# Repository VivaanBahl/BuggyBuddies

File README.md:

# BuggyBuddies
buggy buddies!

LPC Projects: Contains all of the projects that can be opened in LPCXpresso. Each project corresponds to a software component of the buggy.

PWM_Sample: code for the steering controller

Collision_Avoidance: code for the ultrasonic

pwmdemodulator: code for the radio receiver

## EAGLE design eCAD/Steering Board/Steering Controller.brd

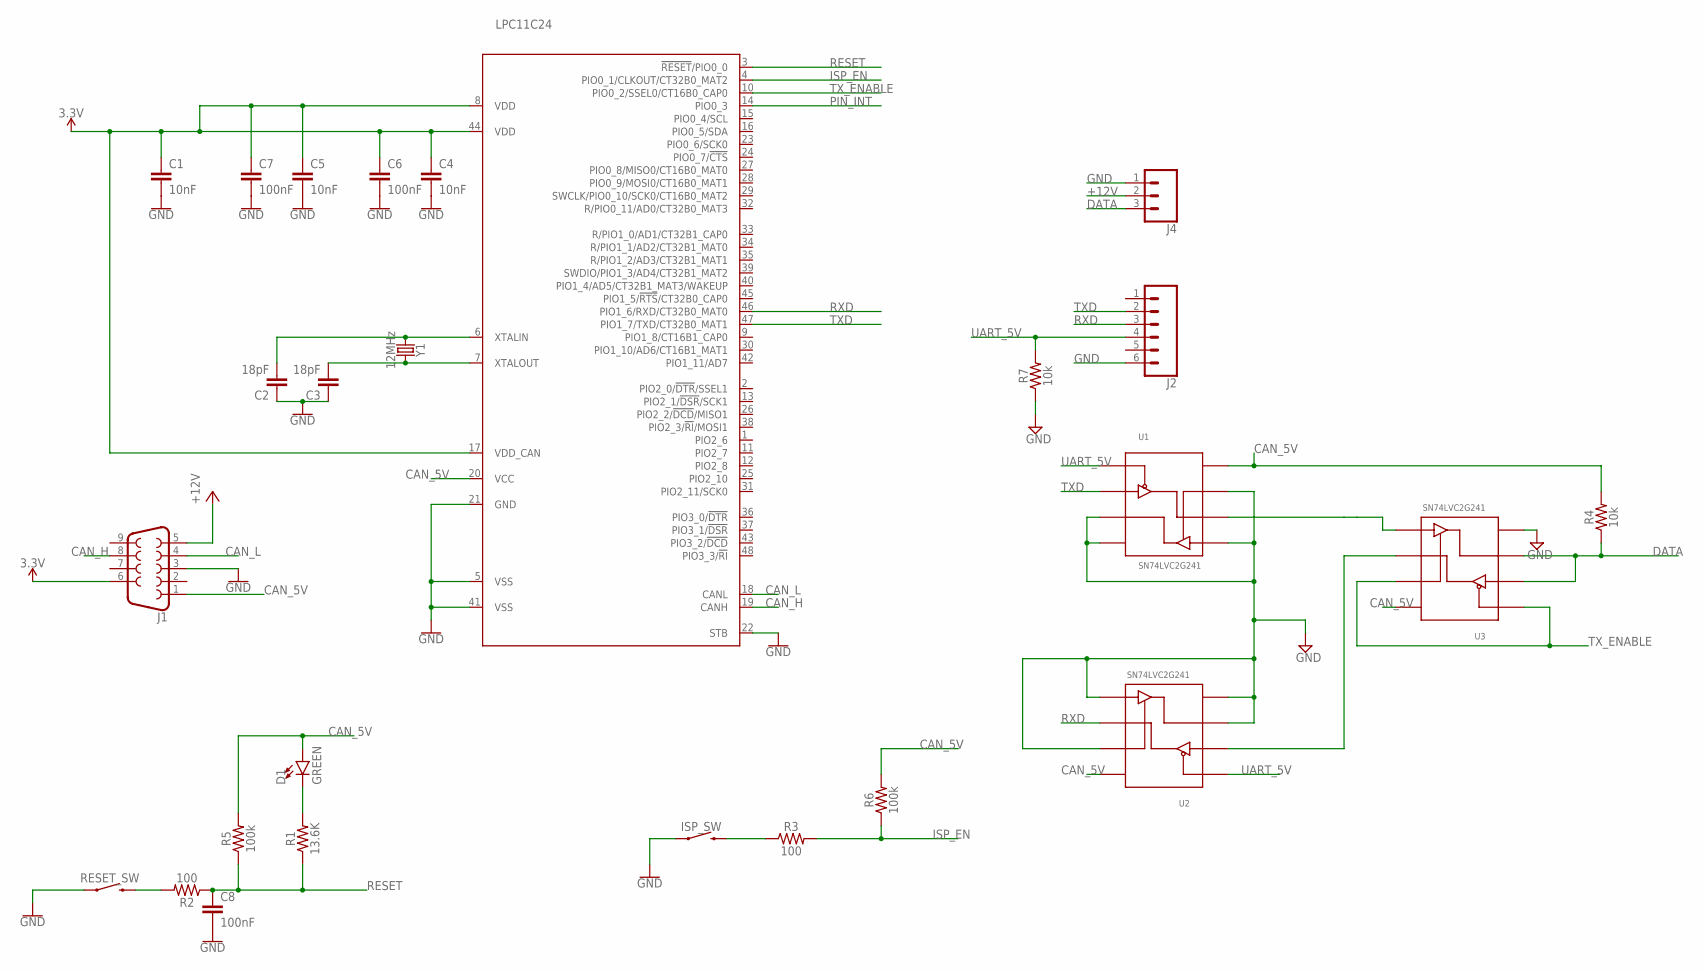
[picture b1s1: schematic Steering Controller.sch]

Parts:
C1, C4, C5: 10nF; CAP-PTH-2.54
C2, C3: 18pF; CAP-PTH-2.54
C6, C7, C8: 100nF; CAP-PTH-2.54
D1: GREEN; LED-1206
ISP_SW: MOMENTARY-SWITCH-SPST-PTH-6.0MM; TACTILE_SWITCH_PTH_6.0MM
J1: DB9FEMALE; DB9
J2: CONN_06SILK_FEMALE_PTH; 1X06
J4: CONN_03; 1X03
LPC11C24: LPC11C22/24-LQFP48; LQFP48
R1: 13.6K; AXIAL-0.3
R2, R3: 100; AXIAL-0.3
R4, R7: 10k; AXIAL-0.3
R5, R6: 100k; AXIAL-0.3
RESET_SW: MOMENTARY-SWITCH-SPST-PTH-6.0MM; TACTILE_SWITCH_PTH_6.0MM
U1, U2, U3: SN74LVC2G241; TI_S8
Y1: 12MHz; HC49US

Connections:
3.3V: C1.1, C4.1, C5.1, C6.1, C7.1, J1.6, LPC11C24.8 (VDD), LPC11C24.17 (VDD_CAN), LPC11C24.44 (VDD)
+12V: J1.5, J4.2
CAN_5V: D1.A, J1.1, LPC11C24.20 (VCC), R4.P$2 (2), R5.P$2 (2), R6.P$2 (2), U1.8 (VCC), U2.8 (VCC), U3.8 (VCC)
CAN_H: J1.8, LPC11C24.19 (CANH)
CAN_L: J1.4, LPC11C24.18 (CANL)
DATA: J4.3, R4.P$1 (1), U3.2 (1IN), U3.3 (2OUT)
GND: C1.2, C2.1, C3.1, C4.2, C5.2, C6.2, C7.2, C8.2, ISP_SW.1, J1.3, J2.6, J4.1, LPC11C24.5 (VSS), LPC11C24.21 (GND), LPC11C24.22 (STB), LPC11C24.41 (VSS), R7.P$1 (1), RESET_SW.1, U1.3 (2OUT), U1.4 (GND), U1.5 (2IN), U1.7 (2OE), U2.3 (2OUT), U2.4 (GND), U2.5 (2IN), U2.7 (2OE), U3.4 (GND)
ISP_EN: LPC11C24.4 (PIO0_1/CLKOUT/CT32B0_MAT2), R3.P$2 (2), R6.P$1 (1)
unnamed: D1.C, R1.P$2 (2)
unnamed: R2.P$2 (2), RESET_SW.3 (2)
unnamed: U2.2 (1IN), U3.6 (1OUT)
unnamed: ISP_SW.3 (2), R3.P$1 (1)
unnamed: U1.6 (1OUT), U3.5 (2IN)
PIN_INT: LPC11C24.14 (PIO0_3)
RESET: C8.1, LPC11C24.3 (!RESET!/PIO0_0), R1.P$1 (1), R2.P$1 (1), R5.P$1 (1)
RXD: J2.3, LPC11C24.46 (PIO1_6/RXD/CT32B0_MAT0), U2.6 (1OUT)
TXD: J2.2, LPC11C24.47 (PIO1_7/TXD/CT32B0_MAT1), U1.2 (1IN)
TX_ENABLE: LPC11C24.10 (PIO0_2/SSEL0/CT16B0_CAP0), U3.1 (~1OE), U3.7 (2OE)
UART_5V: J2.4, R7.P$2 (2), U1.1 (~1OE), U2.1 (~1OE)
XTALIN: C2.2, LPC11C24.6 (XTALIN), Y1.1
XTALOUT: C3.2, LPC11C24.7 (XTALOUT), Y1.2

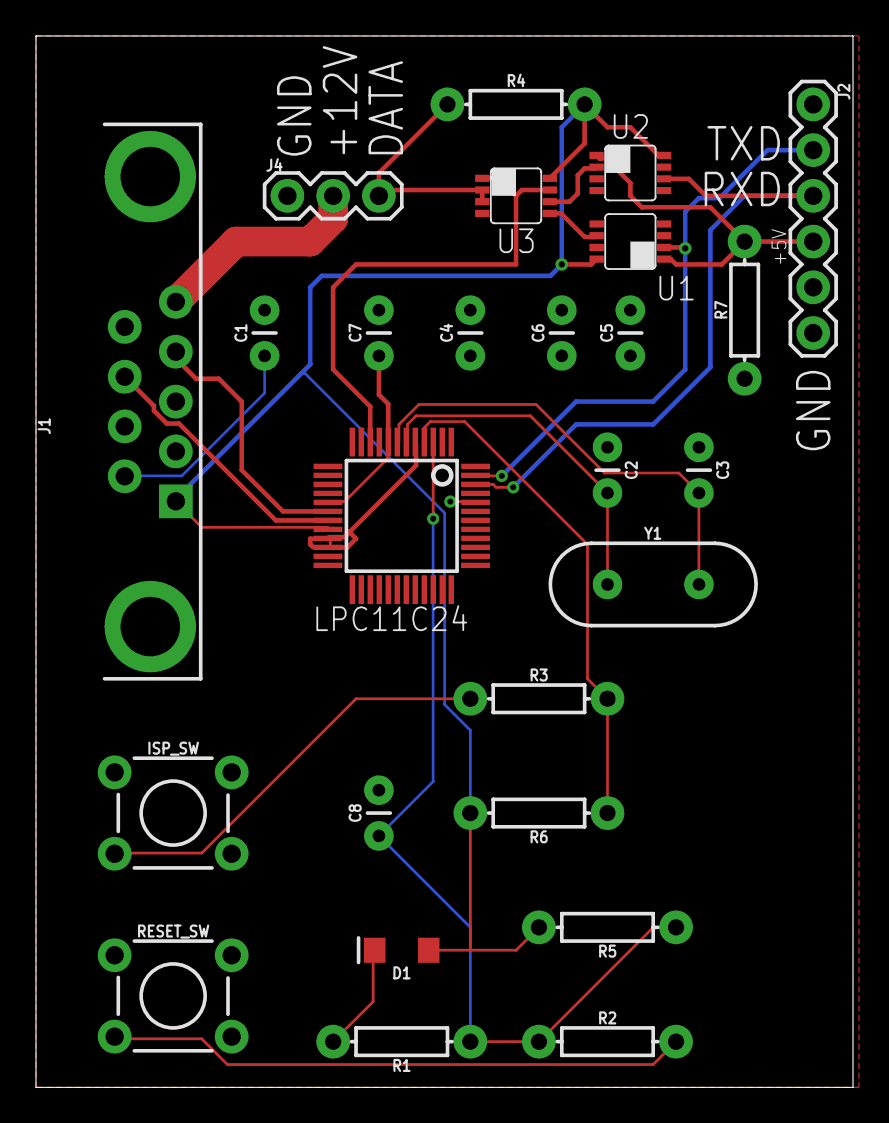
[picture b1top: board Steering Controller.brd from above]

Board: 2 copper layers, 45.4 x 58.4 mm, 26 parts (0 on the bottom side), 20 nets.

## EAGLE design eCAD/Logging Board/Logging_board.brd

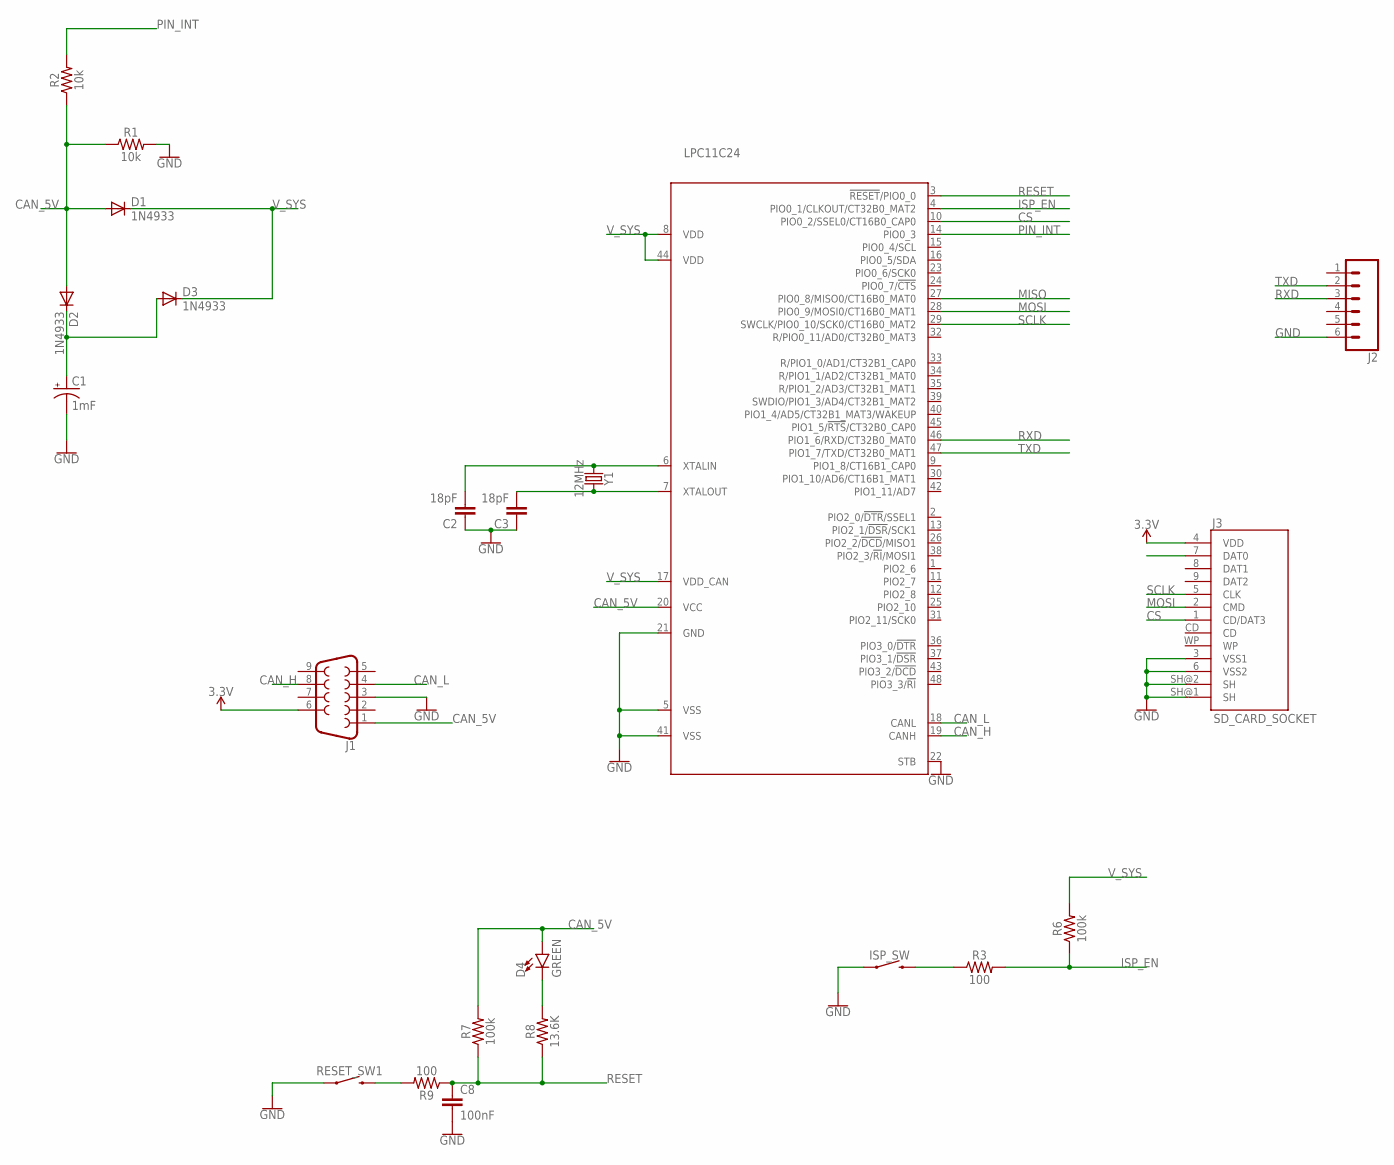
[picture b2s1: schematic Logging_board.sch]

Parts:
C1: 1mF; CPOL-RADIAL-5MM-10MM
C2, C3: 18pF; CAP-PTH-2.54
C8: 100nF; CAP-PTH-2.54
D1, D2, D3: 1N4933; DO41-10
D4: GREEN; LED-1206
ISP_SW: MOMENTARY-SWITCH-SPST-PTH-6.0MM; TACTILE_SWITCH_PTH_6.0MM
J1: DB9FEMALE; DB9
J2: CONN_06SILK_FEMALE_PTH; 1X06
J3: SD_CARD_SOCKET; SD
LPC11C24: LPC11C22/24-LQFP48; LQFP48
R1, R2: 10k; AXIAL-0.3
R3, R9: 100; AXIAL-0.3
R6, R7: 100k; AXIAL-0.3
R8: 13.6K; AXIAL-0.3
RESET_SW1: MOMENTARY-SWITCH-SPST-PTH-6.0MM; TACTILE_SWITCH_PTH_6.0MM
Y1: 12MHz; HC49US

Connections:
3.3V: J1.6, J3.4 (VDD)
CAN_5V: D1.A, D2.A, D4.A, J1.1, LPC11C24.20 (VCC), R1.P$1 (1), R2.P$1 (1), R7.P$2 (2)
CAN_H: J1.8, LPC11C24.19 (CANH)
CAN_L: J1.4, LPC11C24.18 (CANL)
CS: J3.1 (CD/DAT3), LPC11C24.10 (PIO0_2/SSEL0/CT16B0_CAP0)
GND: C1.-, C2.1, C3.1, C8.2, ISP_SW.1, J1.3, J2.6, J3.3 (VSS1), J3.6 (VSS2), J3.SH@1 (SH), J3.SH@2 (SH), LPC11C24.5 (VSS), LPC11C24.21 (GND), LPC11C24.22 (STB), LPC11C24.41 (VSS), R1.P$2 (2), RESET_SW1.1
ISP_EN: LPC11C24.4 (PIO0_1/CLKOUT/CT32B0_MAT2), R3.P$2 (2), R6.P$1 (1)
MISO: LPC11C24.27 (PIO0_8/MISO0/CT16B0_MAT0)
MOSI: J3.2 (CMD), LPC11C24.28 (PIO0_9/MOSI0/CT16B0_MAT1)
unnamed: C1.+, D2.C, D3.A
unnamed: ISP_SW.3 (2), R3.P$1 (1)
unnamed: D4.C, R8.P$2 (2)
unnamed: R9.P$2 (2), RESET_SW1.3 (2)
PIN_INT: LPC11C24.14 (PIO0_3), R2.P$2 (2)
RESET: C8.1, LPC11C24.3 (!RESET!/PIO0_0), R7.P$1 (1), R8.P$1 (1), R9.P$1 (1)
RXD: J2.3, LPC11C24.46 (PIO1_6/RXD/CT32B0_MAT0)
SCLK: J3.5 (CLK), LPC11C24.29 (SWCLK/PIO0_10/SCK0/CT16B0_MAT2)
TXD: J2.2, LPC11C24.47 (PIO1_7/TXD/CT32B0_MAT1)
V_SYS: D1.C, D3.C, LPC11C24.8 (VDD), LPC11C24.17 (VDD_CAN), LPC11C24.44 (VDD), R6.P$2 (2)
XTALIN: C2.2, LPC11C24.6 (XTALIN), Y1.1
XTALOUT: C3.2, LPC11C24.7 (XTALOUT), Y1.2

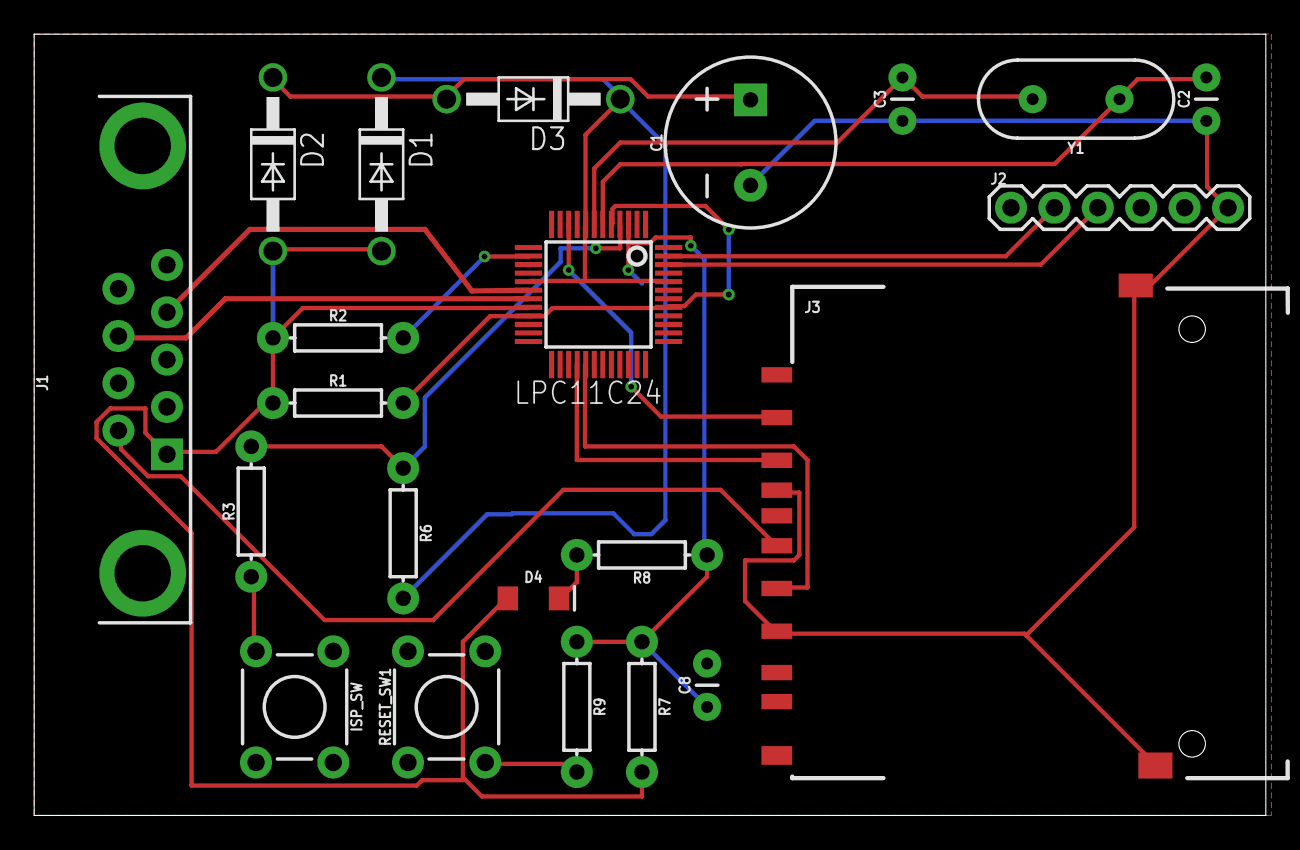
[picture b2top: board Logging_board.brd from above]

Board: 2 copper layers, 72.1 x 45.7 mm, 22 parts (0 on the bottom side), 20 nets.

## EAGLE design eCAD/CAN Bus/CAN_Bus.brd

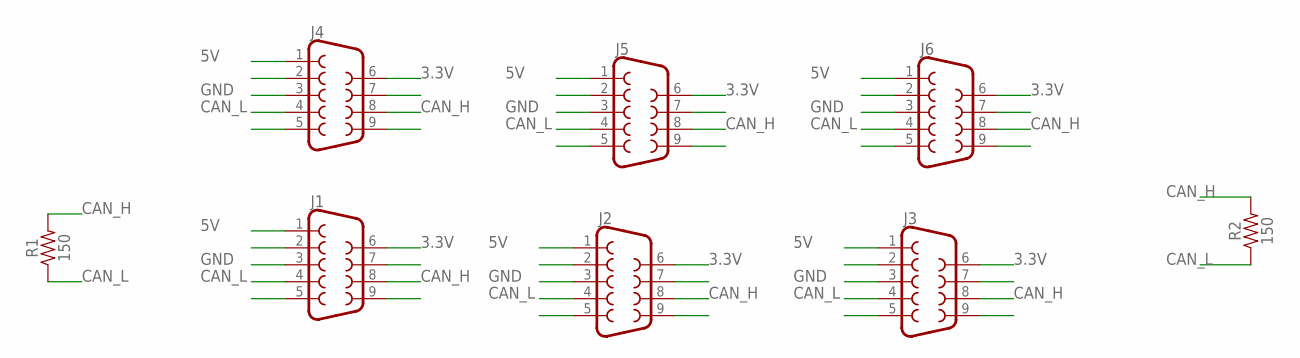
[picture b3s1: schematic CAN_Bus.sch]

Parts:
J1, J2, J3, J4, J5, J6: DB9FEMALE; DB9
R1, R2: 150; AXIAL-0.3

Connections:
3.3V: J1.6, J2.6, J3.6, J4.6, J5.6, J6.6
5V: J1.1, J2.1, J3.1, J4.1, J5.1, J6.1
CAN_H: J1.8, J2.8, J3.8, J4.8, J5.8, J6.8, R1.P$2 (2), R2.P$2 (2)
CAN_L: J1.4, J2.4, J3.4, J4.4, J5.4, J6.4, R1.P$1 (1), R2.P$1 (1)
GND: J1.3, J2.3, J3.3, J4.3, J5.3, J6.3

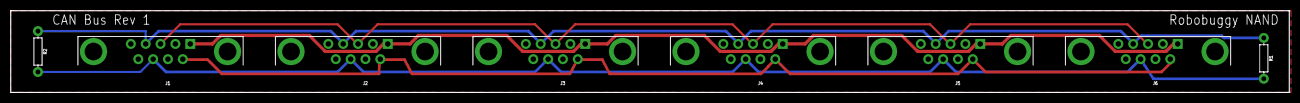
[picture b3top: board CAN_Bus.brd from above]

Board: 2 copper layers, 238.4 x 15.2 mm, 8 parts (0 on the bottom side), 5 nets.

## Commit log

2017-09-28 Added Software folder
2017-09-28 Added empty ROS workspace
2017-09-28 Added in test node
2017-09-28 Added in python nodes folder
2017-09-28 Added message folder
2017-10-07 added FatFs library files
2017-10-07 created dummy project for interacting with files
2017-10-07 actually added the files to the project this time
2017-10-08 CAN bus rev 1. TODO: Send out for manufacturing and test efficacy
2017-10-08 Updating isolation layer to improve PCB fab error tolerance
2017-10-08 Rerouted CAN wires so that wires are of equivalent length
2017-10-08 Increased isolation to 10 mils to add tolerance for manufacturing error
2017-10-09 Added working file read for SPI
2017-10-09 more project config
2017-10-09 Added comment to flowchart for disk init
2017-10-10 Moving boards into their own files. Added diagram for logging board
2017-10-13 Finished ground pour and made all layers visible
2017-10-15 Committing what we have so we can move on to other stuff
2017-10-16 added in PWM sample project
2017-10-17 Made code compatible with Robobuggy library, where each PWM cycle is 5ms, with a 1.5ms neutral
2017-10-17 quadrature encoder should be working, might have included extra files in commit
2017-10-19 updated gitignore to reflect lpc issues
2017-10-19 deleted metadata files
2017-10-19 deleted settings
2017-10-19 Removed metadata files
2017-10-19 deleted more stuff
2017-10-26 put quadrature encoder code in the pwm controller
2017-10-31 Steering on Transistor working!
2017-10-31 rc pwm receiving is working :DDDDDDDD
2017-11-09 Added in ultrasonics code
2017-11-09 demo code
2017-11-09 Fixed the communications issue Turns out it was a faulty pull down resistor
2017-11-12 Rev2 sent out for manufacturing. Added 12MHz oscillator. TODO: Add sign-of-life LED
2017-11-13 PWM demodulator fully functional and able to send received PWM through CAN
2017-11-13 Barebones CAN library with CAN_init, CAN_send, and CAN_receive
2017-11-13 Fixed init function and changed CAN_send to send uint64_t values
2017-11-13 New steering controller pcb.
2017-11-13 Added missing sign-of-life LED and attached Vcc (CAN tranceiver power) to 5V bus
2017-11-14 trying to fix weird bug with CAN_send
2017-11-14 added support for receiving brake and auton pwm signals from the remote control
2017-11-15 Rev1 commit of radio receiver board
2017-11-30 changed IOCON_PIN_B_ID to correct value
2017-11-30 starting to implement sending distances over can
2017-11-30 got multi-can messaging working
2017-12-02 added GPS parser for the ros system
2017-12-02 added basic controller, untested
2017-12-02 Remove dead code
2017-12-02 removed all danger from the code
    now its safe
2017-12-02 Style fixes
2017-12-02 Added uart to can translation
2017-12-02 Added in small sample test project to echo characters back at the user
2017-12-03 some changes to get ultrasonic working on CAN
2017-12-03 addressed sean's comments
2017-12-03 changed so anything written to UART gets echoed out through CAN with mode_id 0x200
2017-12-03 added support for ultrasonic communicating on CAN
2017-12-03 Updating .cproject with postbuild steps to create .hex file for flashing. Updated PID constants to have less jitter
2017-12-04 changed mode_id to 0x100
2017-12-04 hardcoded the triangle waypoints
2017-12-04 commit to work on other stuff
2017-12-04 aded prev orientation
2017-12-04 jetson fixes
2017-12-08 quick
2017-12-12 added info about projects to readme
2017-12-12 fixed pwm sample issues
2017-12-12 renamed danger to collision_detected
2017-12-12 Added in comments
2017-12-12 took out dead code
2017-12-12 cleared up the can library file
2018-03-24 brake message to CAN
2018-03-24 changed msgobj in brakes
2018-03-25 nand steering project
2018-04-01 updated to ring buffer implementation, untested so far
2018-04-01 tested ring buffer code that transmits but does not receive
2018-04-02 Added timer fixes and correct interrupt initialization.
2018-04-03 Added new pin headers & tri-state buffers
    -New 3-pin header to communicate with NAND Servo
    -Removed Obsolete 2pin header
    -Updated DB9 and UART
    -Added Tri-State Buffers to control TXD/RXD data flow.
2018-04-06 Change Tri-State Buffers to 5V
    Also removed extraneous Silkscreen.
2018-09-03 shortened delay that mimics flush in transmitInstructionPacket and commented out ::servo's readStatusPacket call
2018-09-03 implemented sendblocking in ::transmitInstructionPacket method
2018-09-17 dynamixel is receiving instructions but cannot transmit information (as in the case of DServo.read)
2018-09-17 currently, nand steering is not working. we are modifying read status packet so that it does not return error.
2018-09-19 Servo Receiving Commands; ReadRB In Progress
2018-09-29 currently cannot receive can messages in either ccan_rom.c or nand_steering.cpp
2018-11-20 discovered that interrupt handler error occurs when timer initialized

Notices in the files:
parts and their libraries:
SparkFun-Connectors: Licensing: Creative Commons ShareAlike 4.0 International - https://creativecommons.org/licenses/by-sa/4.0
